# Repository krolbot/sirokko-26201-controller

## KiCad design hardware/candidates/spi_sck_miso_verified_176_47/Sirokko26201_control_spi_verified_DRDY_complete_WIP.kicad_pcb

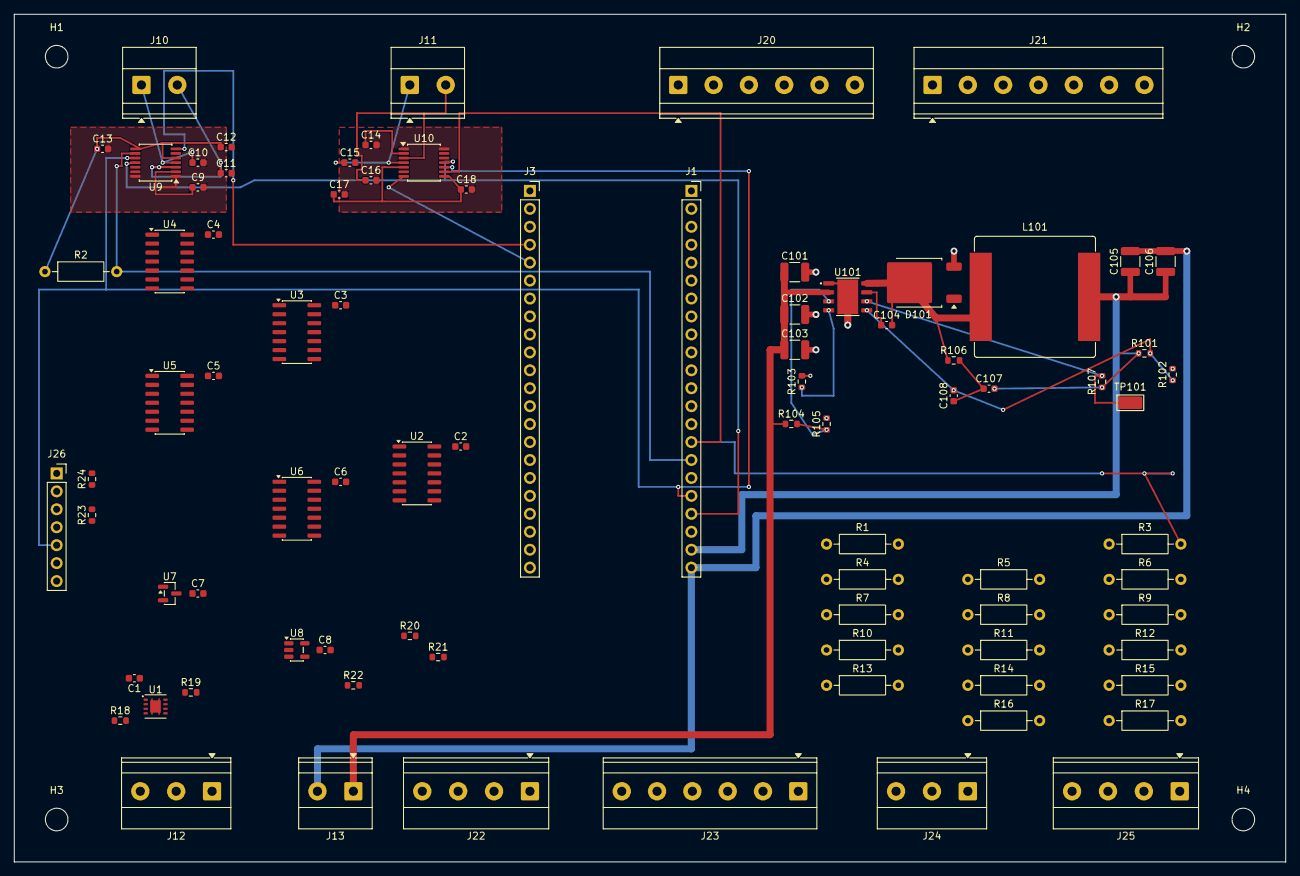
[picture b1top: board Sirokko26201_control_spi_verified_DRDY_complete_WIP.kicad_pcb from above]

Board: 2 copper layers, 180.0 x 120.0 mm, 88 parts (0 on the bottom side), 61 nets.

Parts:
C1, C2, C3, C4, C5, C6, C7, C8: 100n 16V X7R; C_0603_1608Metric
C9, C14: 0.1uF X7R 16V BIAS; C_0603_1608Metric
C10, C15: 0.01uF X7R 16V T+ filter; C_0603_1608Metric
C11, C16: 0.01uF X7R 16V T- filter; C_0603_1608Metric
C12, C17: 0.1uF X7R 16V AVDD; C_0603_1608Metric
C13, C18: 0.1uF X7R 16V DVDD; C_0603_1608Metric
C101, C102: 2.2uF 100V X7R; C_1210_3225Metric
C103: 22uF 100V BULK; C_1210_3225Metric
C104: 2.2nF 50V X7R; C_0603_1608Metric
C105, C106: 47uF 16V X7R; C_1210_3225Metric
C107: 4.7nF 50V C0G; C_0603_1608Metric
C108: 820pF 50V C0G; C_0603_1608Metric
D101: STPS5H100B-TR; TO-252-2
H1, H2, H3, H4: M3; MountingHole_3.2mm_M3
J1: DEVKITC1_J1; PinSocket_1x22_P2.54mm_Vertical
J3: DEVKITC1_J3; PinSocket_1x22_P2.54mm_Vertical
J10: TC_K_EXHAUST_T+_T-; TerminalBlock_Phoenix_MKDS-1,5-2-5.08_1x02_P5.08mm_Horizont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
J11: TC_K_AIR_T+_T-; TerminalBlock_Phoenix_MKDS-1,5-2-5.08_1x02_P5.08mm_Horizont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
J12: ROOM_DS18B20_HARNESS; TerminalBlock_Phoenix_MKDS-1,5-3-5.08_1x03_P5.08mm_Horizont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
J13: 24V_LOGIC_INPUT_ONLY__DRAFT_NOT_FOR_ORDER; TerminalBlock_Phoenix_MKDS-1,5-2-5.08_1x02_P5.08mm_Horizont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
J20: DRIVER_LOGIC_3V3_ONLY; TerminalBlock_Phoenix_MKDS-1,5-6_1x06_P5.00mm_Horizontal
J21: SAFETY_MONITOR_3V3_NO_EXT_DRIVE; TerminalBlock_Phoenix_MKDS-1,5-7_1x07_P5.00mm_Horizontal
J22: PANEL_DRY_CONTACTS_3V3; TerminalBlock_Phoenix_MKDS-1,5-4-5.08_1x04_P5.08mm_Horizont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
J23: LOCAL_BUTTONS_3V3__SET_UP_DOWN_PRESERVED; TerminalBlock_Phoenix_MKDS-1,5-6_1x06_P5.00mm_Horizontal
J24: RESET_HW_SPDT_BBM_3V3; TerminalBlock_Phoenix_MKDS-1,5-3-5.08_1x03_P5.08mm_Horizont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
J25: THERMAL_AND_HW_ENABLE_3V3_ONLY; TerminalBlock_Phoenix_MKDS-1,5-4-5.08_1x04_P5.08mm_Horizont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
J26: TFT_GMT020-02-7P_ST7789V_7P_SOCKET__FOOTPRINT_NOT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; PinSocket_1x07_P2.54mm_Vertical
L101: 33uH Isat>=10A; L_Bourns_SRP1770TA_16.9x16.9mm
R1: 4k7; R_Axial_DIN0207_L6.3mm_D2.5mm_P10.16mm_Horizontal
R2, R3, R4, R5, R6, R7, R8, R9, R10, R11, R12, R13, R14, R15, R16, R17: 10k; R_Axial_DIN0207_L6.3mm_D2.5mm_P10.16mm_Horizontal
R18, R19, R20, R21, R22, R102, R105, R107: 10k 1%; R_0603_1608Metric
R23: 33R TFT_RESET_SERIES; R_0603_1608Metric
R24: 10k TFT_CS_PULLUP; R_0603_1608Metric
R101, R103: 31.6k 1%; R_0603_1608Metric
R104: 100k 1%; R_0603_1608Metric
R106: 82k 1%; R_0603_1608Metric
TP101: PGOOD_5V_NOT_GPIO; TestPoint_Keystone_5015_Micro_Mini
U1: TPS3431SDRBR; TPS3431_DRB0008A
U2: SN74HCS74D; SOIC-14_3.9x8.7mm_P1.27mm
U3: SN74HCS14D; SOIC-14_3.9x8.7mm_P1.27mm
U4, U5: SN74HCS30D; SOIC-14_3.9x8.7mm_P1.27mm
U6: SN74HCS11D; SOIC-14_3.9x8.7mm_P1.27mm
U7: TPS3839G33DBZR; SOT-23
U8: SN74LVC1G14DBVR; SOT-23-5
U9, U10: MAX31856MUD+; TSSOP-14_4.4x5mm_P0.65mm
U101: LM5013DDAR; DDA0008B_LM5013DDAR_TI4214849B

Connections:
+5V_DEVKIT: C105.1, C106.1, C107.2, J1.21, L101.2, R101.1, R107.1
/+3V3: C1.1, C2.1, C3.1, C4.1, C5.1, C6.1, C7.1, C8.1, C12.1, C13.1, C17.1, C18.1, J1.1, J1.2, J12.1, J21.2, J23.2, J25.1, J26.6, R1.1, R2.1, R3.1, R13.1, R14.1, R15.1, R16.1, R17.1, R18.1, R19.1, R20.1, R21.1, R24.2, U1.1, U1.3, U1.5, U2.4, U2.14, U3.14, U4.11, U4.12, U4.14, U5.6, U5.11, U5.12, U5.14, U6.5, U6.13, U6.14, U7.3, U8.5, U9.5, U9.8, U10.5, U10.8
/ALLOW_LATCH: U2.5, U6.1
/ARM_READY: J3.7, J21.5, R10.1, U4.5, U5.1
/CLEAR_OK: U2.1, U3.10, U6.2
/EN_CHIP_PU: J1.3, R23.1
/EXT_SAFETY_ENABLE: J25.4, U6.6
/FAN_REQUEST: J1.9, J20.5, R7.1
/FUEL_CMD: J1.8, J20.3, R5.1, U3.3
/FUEL_PERMIT: J3.18, J20.4, R6.1, U3.5, U6.4
/GLOW_CMD: J1.20, J20.2, R4.1, U3.9
/GND: C1.2, C2.2, C3.2, C4.2, C5.2, C6.2, C7.2, C8.2, C9.2, C10.2, C11.2, C12.2, C13.2, C14.2, C15.2, C16.2, C17.2, C18.2, C101.2, C102.2, C103.2, C105.2, C106.2, D101.3, J1.22, J3.1, J3.21, J3.22, J12.3, J13.2, J20.1, J21.1, J22.1, J23.1, J24.1, J25.3, J26.7, R4.2, R5.2, R6.2, R7.2, R8.2, R9.2, R10.2, R11.2, R12.2, R22.2, R102.2, R103.2, R105.2, U1.4, U1.9, U2.7, U2.11, U2.12, U3.7, U4.7, U5.7, U6.7, U6.9, U6.10, U6.11, U7.1, U8.3, U9.1, U9.14, U10.1, U10.14, U101.1, U101.9
/HW_RESET_CLK: U2.3, U2.9
/LOGIC_POWER_24_TO_5V__DRAFT_NOT_FOR_ORDER/BOOT: C104.1, U101.7
/LOGIC_POWER_24_TO_5V__DRAFT_NOT_FOR_ORDER/EN_LOGIC: R104.2, R105.1, U101.3
/LOGIC_POWER_24_TO_5V__DRAFT_NOT_FOR_ORDER/FB: C108.2, R101.2, R102.1, U101.5
/LOGIC_POWER_24_TO_5V__DRAFT_NOT_FOR_ORDER/PGOOD_5V: R107.2, TP101.1, U101.6
/LOGIC_POWER_24_TO_5V__DRAFT_NOT_FOR_ORDER/RAMP: C107.1, C108.1, R106.2
/LOGIC_POWER_24_TO_5V__DRAFT_NOT_FOR_ORDER/RON: R103.1, U101.4
/LOGIC_POWER_24_TO_5V__DRAFT_NOT_FOR_ORDER/SW: C104.2, D101.2, L101.1, R106.1, U101.8
/NOT_CLEAR_OK: U3.11, U4.8
/NOT_FUEL_CMD: U3.4, U5.2
/NOT_FUEL_PERMIT: U3.6, U5.3
/NOT_GLOW_CMD: U3.8, U5.4
/NOT_RESET_ACCEPT: U3.13, U5.8
/NOT_SW_TRIP: U3.2, U4.6
/P24_PROTECTED: C101.1, C102.1, C103.1, J13.1, R104.1, U101.2
/PG_OK: U4.1, U7.2
/RESET_ACCEPT: U2.2, U3.12
/RESET_HW_NC_N: J24.2, R20.2, U2.13
/RESET_HW_NO_N: J24.3, R21.2, U2.10
/RESET_REQUEST: J1.6, J21.7, J22.2, R13.2
/ROOM_DQ: J1.4, J12.2, R1.2
/SAFETY_OK: J1.5, J21.6, R12.1, U6.3, U6.12
/SET_DOWN_REQUEST: J3.8, J23.6, R17.2
/SET_UP_REQUEST: J3.9, J23.5, R16.2
/SPEED_CMD: J1.10, J20.6, R8.1
/START_REQUEST: J1.7, J22.3, R14.2, U5.5
/STOP_OK: U4.3, U8.4
/STOP_STATUS: J1.12, J22.4, R15.2, U8.2
/SW_TRIP: J3.6, J21.4, R11.1, U3.1
/TC_AIR_BIAS: C14.1, U10.2
/TC_AIR_CS: J1.15, R3.2, U10.9
/TC_AIR_DRDY: J3.5, U10.7
/TC_AIR_TM: C16.1, J11.2, U10.3
/TC_AIR_TP: C15.1, J11.1, U10.4
/TC_EXH_BIAS: C9.1, U9.2
/TC_EXH_CS: J1.16, R2.2, U9.9
/TC_EXH_DRDY: J3.4, U9.7
/TC_EXH_TM: C11.1, J10.2, U9.3
/TC_EXH_TP: C10.1, J10.1, U9.4
/TC_SCK: J1.18, J26.5, U9.10, U10.10
/TC_SDI_MOSI: J1.17, J26.4, U9.12, U10.12
/TC_SDO_MISO: J1.19, U9.11, U10.11
/TFT_CS: J3.17, J26.1, R24.1
/TFT_DC: J3.16, J26.2
/TFT_RESET_N: J26.3, R23.2
/THERMAL_OK: J25.2, R22.1, U4.4
/WD_CWD_FIXED: R18.2, U1.2
/WD_HEARTBEAT: J1.11, J21.3, R9.1, U1.6
/WD_OK: R19.2, U1.7, U1.8, U4.2
